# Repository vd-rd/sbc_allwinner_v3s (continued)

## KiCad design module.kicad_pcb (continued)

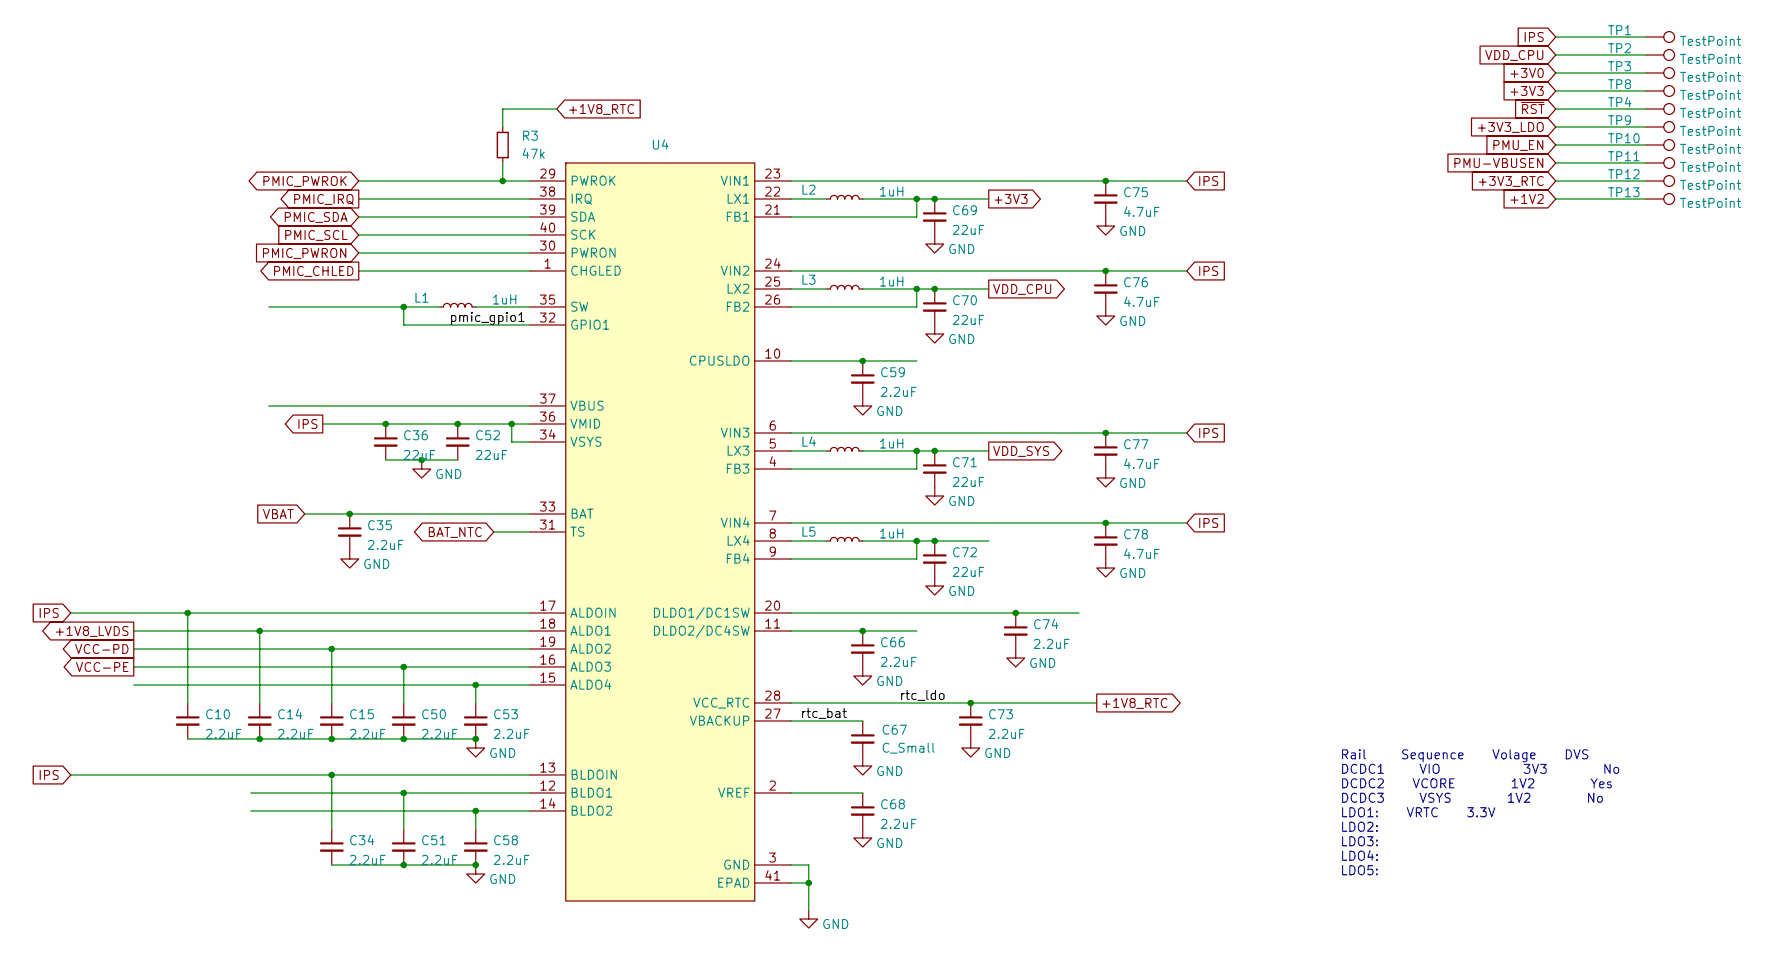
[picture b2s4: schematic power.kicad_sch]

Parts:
C10, C14, C15, C34, C35, C50, C51, C53, C58, C59, C66, C68, C73, C74: 2.2uF; C_0402_1005Metric
C36, C52, C69, C70, C71, C72: 22uF; C_0805_2012Metric
C67: C_Small; C_1210_3225Metric
C75, C76, C77, C78: 4.7uF; C_0603_1608Metric
L1, L2, L3, L4, L5: 1uH; L_Wuerth_MAPI-2512
R3: 47k; R_0402_1005Metric
TP1, TP2, TP3, TP4, TP8, TP9, TP10, TP11, TP12, TP13: TestPoint; TestPoint_Pad_D1.0mm
U4: QFN-40-1EP_5x5mm_P0.4mm_EP3.8x3.8mm_ThermalVias

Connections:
+1V2: TP13.1; also elsewhere on the board
+1V8_LVDS: C14.1, U4.18 (ALDO1)
+1V8_RTC: C73.1, R3.2, U4.28 (VCC_RTC)
+3V0: TP3.1; also elsewhere on the board
+3V3: C69.1, L2.2, TP8.1, U4.21 (FB1); also elsewhere on the board
+3V3_LDO: TP9.1; also elsewhere on the board
+3V3_RTC: TP12.1; also elsewhere on the board
/power/pmic_gpio1: L1.1, U4.32 (GPIO1)
/power/rtc_bat: C67.1, U4.27 (VBACKUP)
BAT_NTC: U4.31 (TS)
GND: C10.2, C14.2, C15.2, C34.2, C35.2, C36.2, C50.2, C51.2, C52.2, C53.2, C58.2, C59.2, C66.2, C67.2, C68.2, C69.2, C70.2, C71.2, C72.2, C73.2, C74.2, C75.2, C76.2, C77.2, C78.2, U4.3 (GND), U4.41 (EPAD); also elsewhere on the board
IPS: C10.1, C34.1, C36.1, C52.1, C75.1, C76.1, C77.1, C78.1, TP1.1, U4.6 (VIN3), U4.7 (VIN4), U4.13 (BLDOIN), U4.17 (ALDOIN), U4.23 (VIN1), U4.24 (VIN2), U4.34 (VSYS), U4.36 (VMID)
unnamed: C53.1, U4.15 (ALDO4)
unnamed: C51.1, U4.12 (BLDO1)
unnamed: C58.1, U4.14 (BLDO2)
unnamed: C59.1, U4.10 (CPUSLDO)
unnamed: C74.1, U4.20 (DLDO1/DC1SW)
unnamed: C66.1, U4.11 (DLDO2/DC4SW)
unnamed: C72.1, L5.2, U4.9 (FB4)
unnamed: L2.1, U4.22 (LX1)
unnamed: L3.1, U4.25 (LX2)
unnamed: L4.1, U4.5 (LX3)
unnamed: L5.1, U4.8 (LX4)
unnamed: L1.2, U4.35 (SW)
unnamed: C68.1, U4.2 (VREF)
PMIC_CHLED: U4.1 (CHGLED)
PMIC_IRQ: U4.38 (IRQ)
PMIC_PWROK: R3.1, U4.29 (PWROK)
PMIC_PWRON: U4.30 (PWRON)
PMIC_SCL: U4.40 (SCK)
PMIC_SDA: U4.39 (SDA)
PMU-VBUSEN: TP11.1; also elsewhere on the board
PMU_EN: TP10.1
VBAT: C35.1, U4.33 (BAT)
VCC-PD: C15.1, U4.19 (ALDO2)
VCC-PE: C50.1, U4.16 (ALDO3)
VDD_CPU: C70.1, L3.2, TP2.1, U4.26 (FB2); also elsewhere on the board
VDD_SYS: C71.1, L4.2, U4.4 (FB3)
~RST: TP4.1; also elsewhere on the board

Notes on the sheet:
Rail Sequence Volage DVS DCDC1 VIO 3V3 No DCDC2 VCORE 1V2 Yes DCDC3 VSYS 1V2 No LDO1: VRTC 3.3V LDO2: LDO3: LDO4: LDO5:

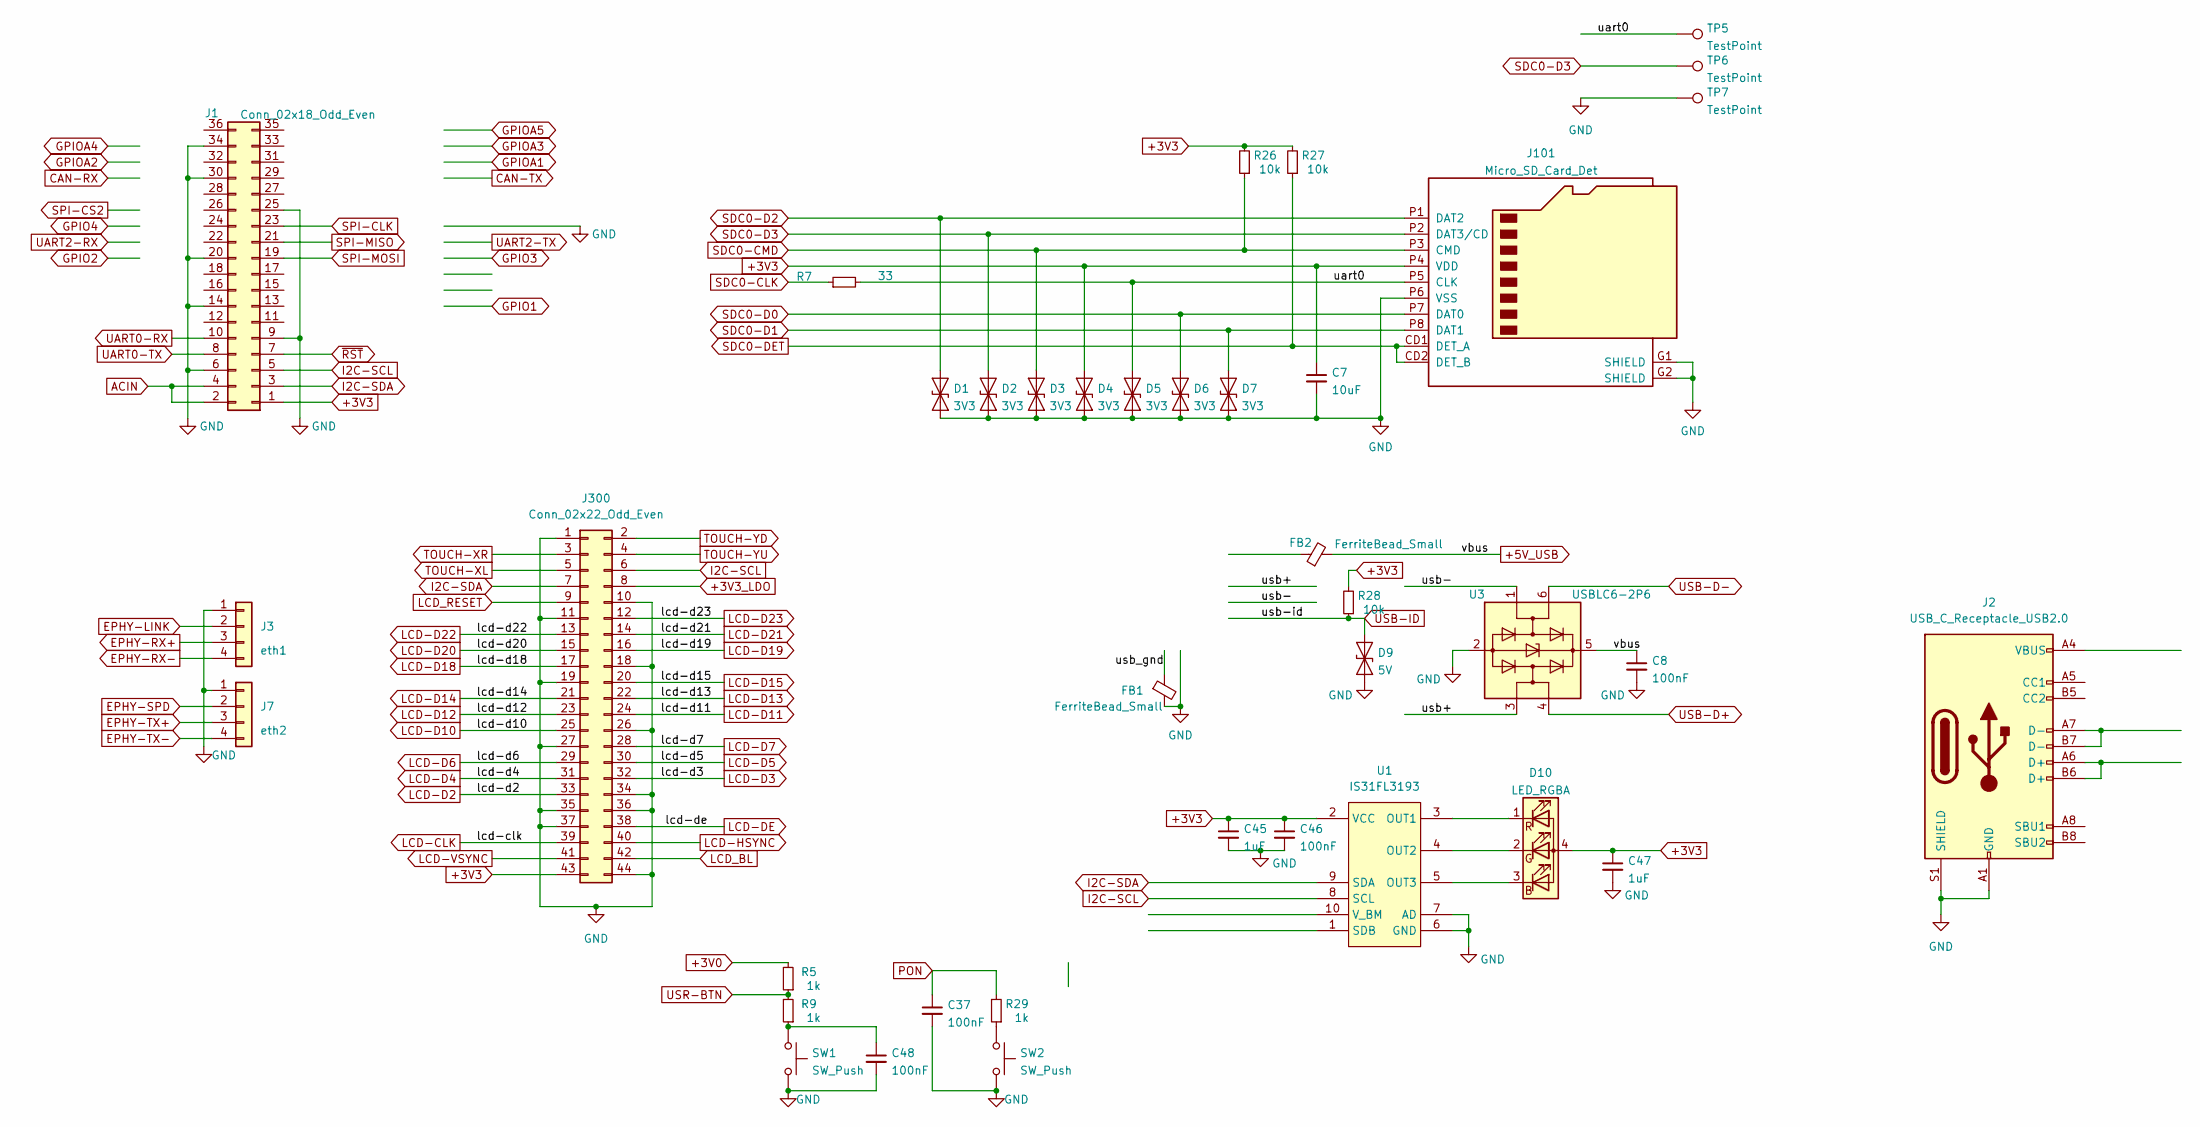
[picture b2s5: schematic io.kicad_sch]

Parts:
C7: 10uF; C_0603_1608Metric
C8, C37, C46, C48: 100nF; C_0402_1005Metric
C45, C47: 1uF; C_0402_1005Metric
D1, D2, D3, D4, D5, D6, D7: 3V3; D_SOD-923
D9: 5V; D_SOD-923
D10: LED_RGBA; rgb-1204
FB1, FB2: FerriteBead_Small; R_0603_1608Metric
J1: Conn_02x18_Odd_Even; PinHeader_2x18_P2.54mm_Vertical
J2: USB_C_Receptacle_USB2.0; USB_C_Receptacle_GCT_USB4085
J3: eth1; PinHeader_2x02_P1.27mm_Vertical
J7: eth2; PinHeader_2x02_P1.27mm_Vertical
J101: Micro_SD_Card_Det; MEM20610118800A
J300: Conn_02x22_Odd_Even; PinHeader_2x22_P1.27mm_Vertical
R5, R9, R29: 1k; R_0402_1005Metric
R7: 33; R_0402_1005Metric
R26, R27, R28: 10k; R_0402_1005Metric
SW1, SW2: SW_Push; SW_SPST_EVQP7C
TP5, TP6, TP7: TestPoint; TestPoint_Pad_D1.0mm
U1: IS31FL3193; DFN-10-1EP_3x3mm_P0.5mm_EP1.7x2.5mm
U3: USBLC6-2P6; SOT-23-6

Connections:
+3V0: R5.2; also elsewhere on the board
+3V3: C7.1, C45.1, C46.1, C47.1, D4.2 (A2), D10.4 (A), J1.1, J101.P4 (VDD), J300.43, R26.2, R27.2, R28.2, U1.2 (VCC); also elsewhere on the board
+3V3_LDO: J300.8; also elsewhere on the board
+5V_USB: C8.1, FB2.2, U3.5 (VBUS)
/io/uart0: D5.2 (A2), J101.P5 (CLK), R7.2, TP5.1
/io/usb+: U3.3 (I/O2)
/io/usb-: U3.1 (I/O1)
/io/usb_gnd: FB1.1
ACIN: J1.2, J1.4
EPHY-LINK: J3.2; also elsewhere on the board
EPHY-RX+: J3.3; also elsewhere on the board
EPHY-RX-: J3.4; also elsewhere on the board
EPHY-SPD: J7.2; also elsewhere on the board
EPHY-TX+: J7.3; also elsewhere on the board
EPHY-TX-: J7.4; also elsewhere on the board
GND: C7.2, C8.2, C37.2, C45.2, C46.2, C47.2, C48.2, D1.1 (A1), D2.1 (A1), D3.1 (A1), D4.1 (A1), D5.1 (A1), D6.1 (A1), D7.1 (A1), D9.1 (A1), FB1.2, J1.6, J1.9, J1.14, J1.20, J1.25, J1.30, J1.34, J2.A1 (GND), J2.A12 (GND), J2.B1 (GND), J2.B12 (GND), J2.S1 (SHIELD), J3.1, J7.1, J101.G1 (SHIELD), J101.G2 (SHIELD), J101.P6 (VSS), J300.1, J300.10, J300.11, J300.18, J300.19, J300.26, J300.27, J300.34, J300.35, J300.36, J300.37, J300.44, SW1.2, SW2.2, TP7.1, U1.6 (GND), U1.7 (AD), U1.11 (GND), U3.2 (GND); also elsewhere on the board
I2C-SCL: J1.5, J300.6, U1.8 (SCL); also elsewhere on the board
I2C-SDA: J1.3, J300.7, U1.9 (SDA); also elsewhere on the board
LCD-CLK: J300.39; also elsewhere on the board
LCD-D2: J300.33; also elsewhere on the board
LCD-D3: J300.32; also elsewhere on the board
LCD-D4: J300.31; also elsewhere on the board
LCD-D5: J300.30; also elsewhere on the board
LCD-D6: J300.29; also elsewhere on the board
LCD-D7: J300.28; also elsewhere on the board
LCD-D10: J300.25; also elsewhere on the board
LCD-D11: J300.24; also elsewhere on the board
LCD-D12: J300.23; also elsewhere on the board
LCD-D13: J300.22; also elsewhere on the board
LCD-D14: J300.21; also elsewhere on the board
LCD-D15: J300.20; also elsewhere on the board
LCD-D18: J300.17; also elsewhere on the board
LCD-D19: J300.16; also elsewhere on the board
LCD-D20: J300.15; also elsewhere on the board
LCD-D21: J300.14; also elsewhere on the board
LCD-D22: J300.13; also elsewhere on the board
LCD-D23: J300.12; also elsewhere on the board
LCD-DE: J300.38; also elsewhere on the board
LCD-HSYNC: J300.40; also elsewhere on the board
LCD-VSYNC: J300.41; also elsewhere on the board
LCD_BL: J300.42; also elsewhere on the board
LCD_RESET: J300.9
unnamed: C48.1, R9.1, SW1.1
unnamed: D10.3 (BK), U1.5 (OUT3)
unnamed: D10.2 (GK), U1.4 (OUT2)
unnamed: D10.1 (RK), U1.3 (OUT1)
unnamed: J2.A6 (D+), J2.B6 (D+)
unnamed: J2.A7 (D-), J2.B7 (D-)
unnamed: J2.A4 (VBUS), J2.A9 (VBUS), J2.B4 (VBUS), J2.B9 (VBUS)
unnamed: R29.1, SW2.1
PON: C37.1, R29.2
SDC0-CLK: R7.1; also elsewhere on the board
SDC0-CMD: D3.2 (A2), J101.P3 (CMD), R26.1; also elsewhere on the board
SDC0-D0: D6.2 (A2), J101.P7 (DAT0); also elsewhere on the board
SDC0-D1: D7.2 (A2), J101.P8 (DAT1); also elsewhere on the board
SDC0-D2: D1.2 (A2), J101.P1 (DAT2); also elsewhere on the board
SDC0-D3: D2.2 (A2), J101.P2 (DAT3/CD), TP6.1; also elsewhere on the board
SDC0-DET: J101.CD1 (DET_A), J101.CD2 (DET_B), R27.1; also elsewhere on the board
TOUCH-XL: J300.5
TOUCH-XR: J300.3
TOUCH-YD: J300.2
TOUCH-YU: J300.4
USB-D+: U3.4 (I/O2); also elsewhere on the board
USB-D-: U3.6 (I/O1); also elsewhere on the board
USB-ID: D9.2 (A2), R28.1; also elsewhere on the board
USR-BTN: R5.1, R9.2; also elsewhere on the board

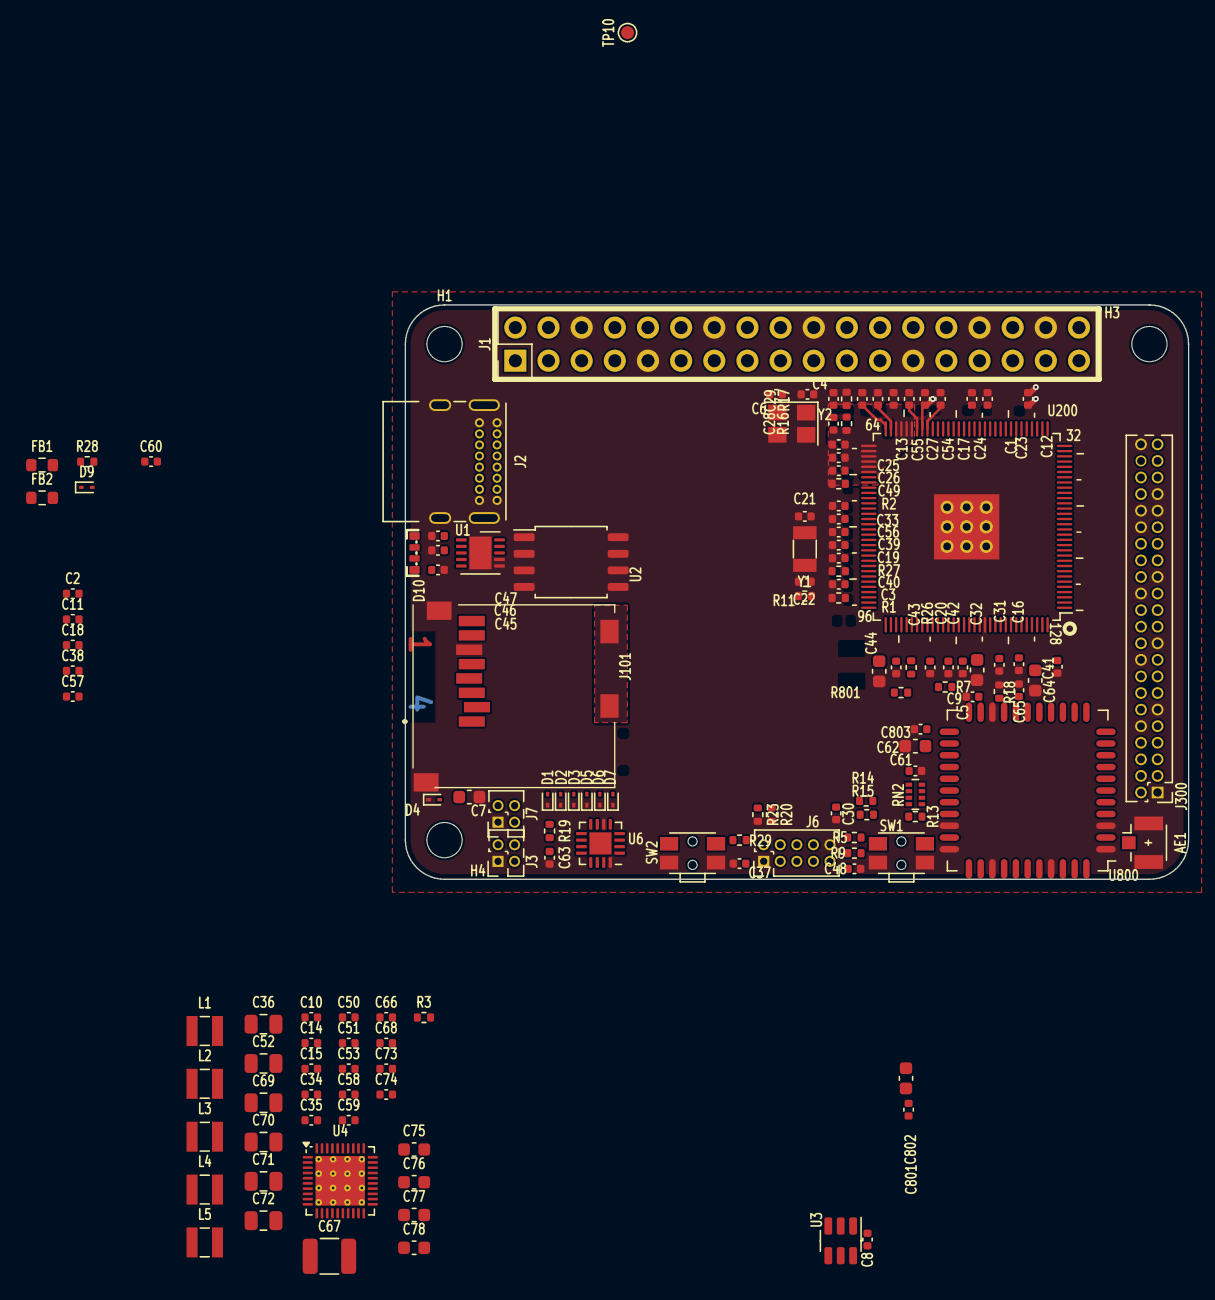
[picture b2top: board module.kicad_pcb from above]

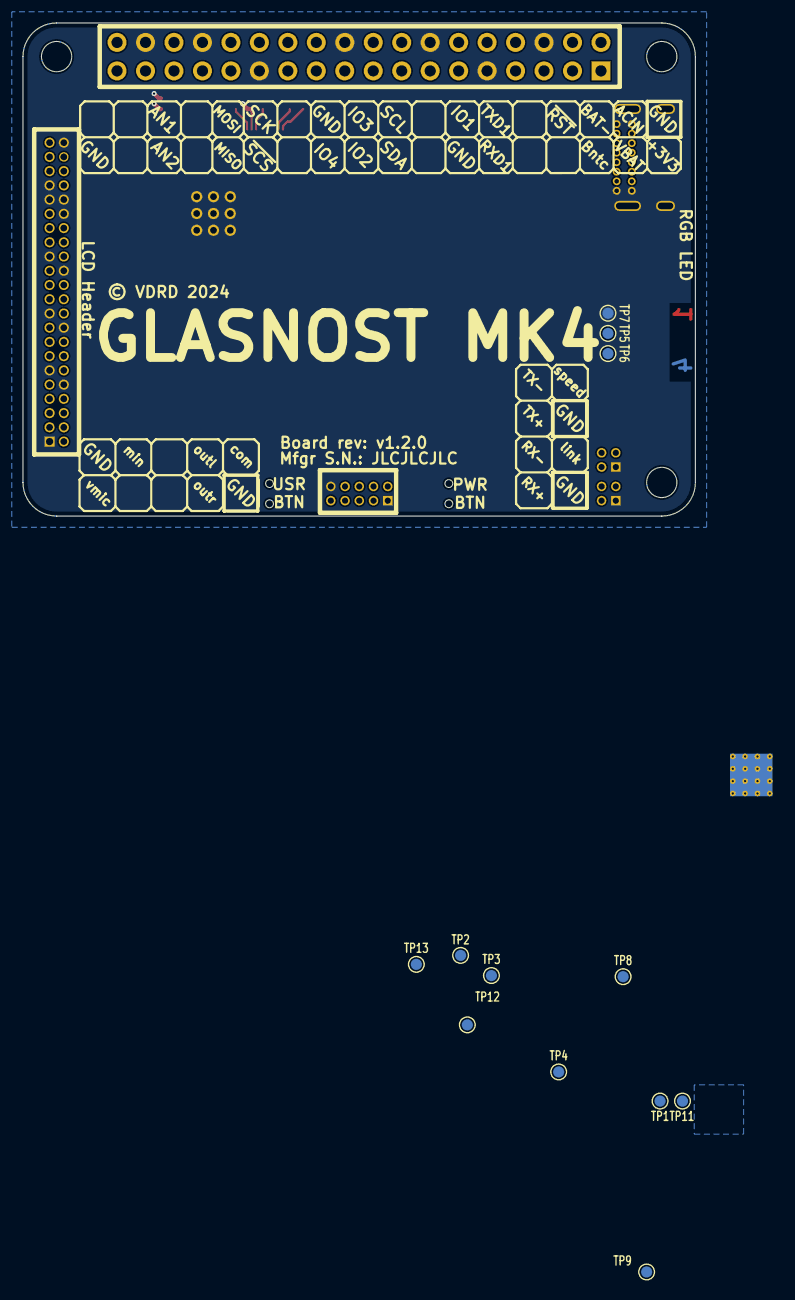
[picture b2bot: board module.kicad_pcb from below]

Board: 4 copper layers, 60.0 x 44.0 mm, 154 parts (12 on the bottom side), 125 nets.

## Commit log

2019-01-22 repo bringup
2019-05-02 project: updated structure
2019-05-15 board: updated flooplan
2019-05-17 board: added nvm storage
2019-05-17 defined power stage
2019-11-22 project: refactor board with new specs
2021-10-04 switch to kicad
2021-10-06 updates on features and layout
2021-10-10 improve component placement
2021-10-16 added proper pmic
2021-10-23 upadted dimensions and component positions
2021-10-23 cosmetic fixes
2021-10-24 swap pmic section with axp203
2021-10-25 added 3d models
2021-10-26 arranged parts for pmic
2021-11-01 routed axp203 and optimized component footprints
2021-11-13 small fixes
2022-01-04 prepare for component reposition
2022-01-10 change component layout
2022-01-10 defined cpu connections
2022-01-11 routed lcd signals
2022-01-14 routed lcd bus
2022-01-16 add layer identification labels
2022-01-25 small layout tweaks
2022-01-29 remove lcd fpc connector
2022-01-30 add datasheet and new lcd connector
2022-02-25 change cpu footprint
2022-03-08 try new component placement
2022-03-24 add axp203 aux parts
2022-03-28 routing work
2022-03-29 added more testpoints
2022-03-30 add 5v otg support components
2022-04-16 add board render
2022-05-03 add spi flash for boot
2022-05-04 finish lcd bus
2022-05-06 prepare wifi section and io exp
2022-05-07 add wifi parts
2022-05-07 add missing 3d models
2022-05-07 add port expander for additional gpio
2022-05-12 define lcd connector pins
2022-05-13 add port expander connections
2022-05-22 fix ethernet header for compatibility
2022-05-26 more routing work
2022-05-26 fix audio connector
2022-05-26 finished routing
2022-06-16 updated board
2022-07-10 prepare first release for fab
2024-03-08 new layout
2024-06-22 simplified the design
2024-10-28 [WIP] Rework power tree
2025-01-10 rework component placement
2026-01-04 prepare for rev2
2026-01-26 placed decoupling caps
2026-04-22 backport changes
